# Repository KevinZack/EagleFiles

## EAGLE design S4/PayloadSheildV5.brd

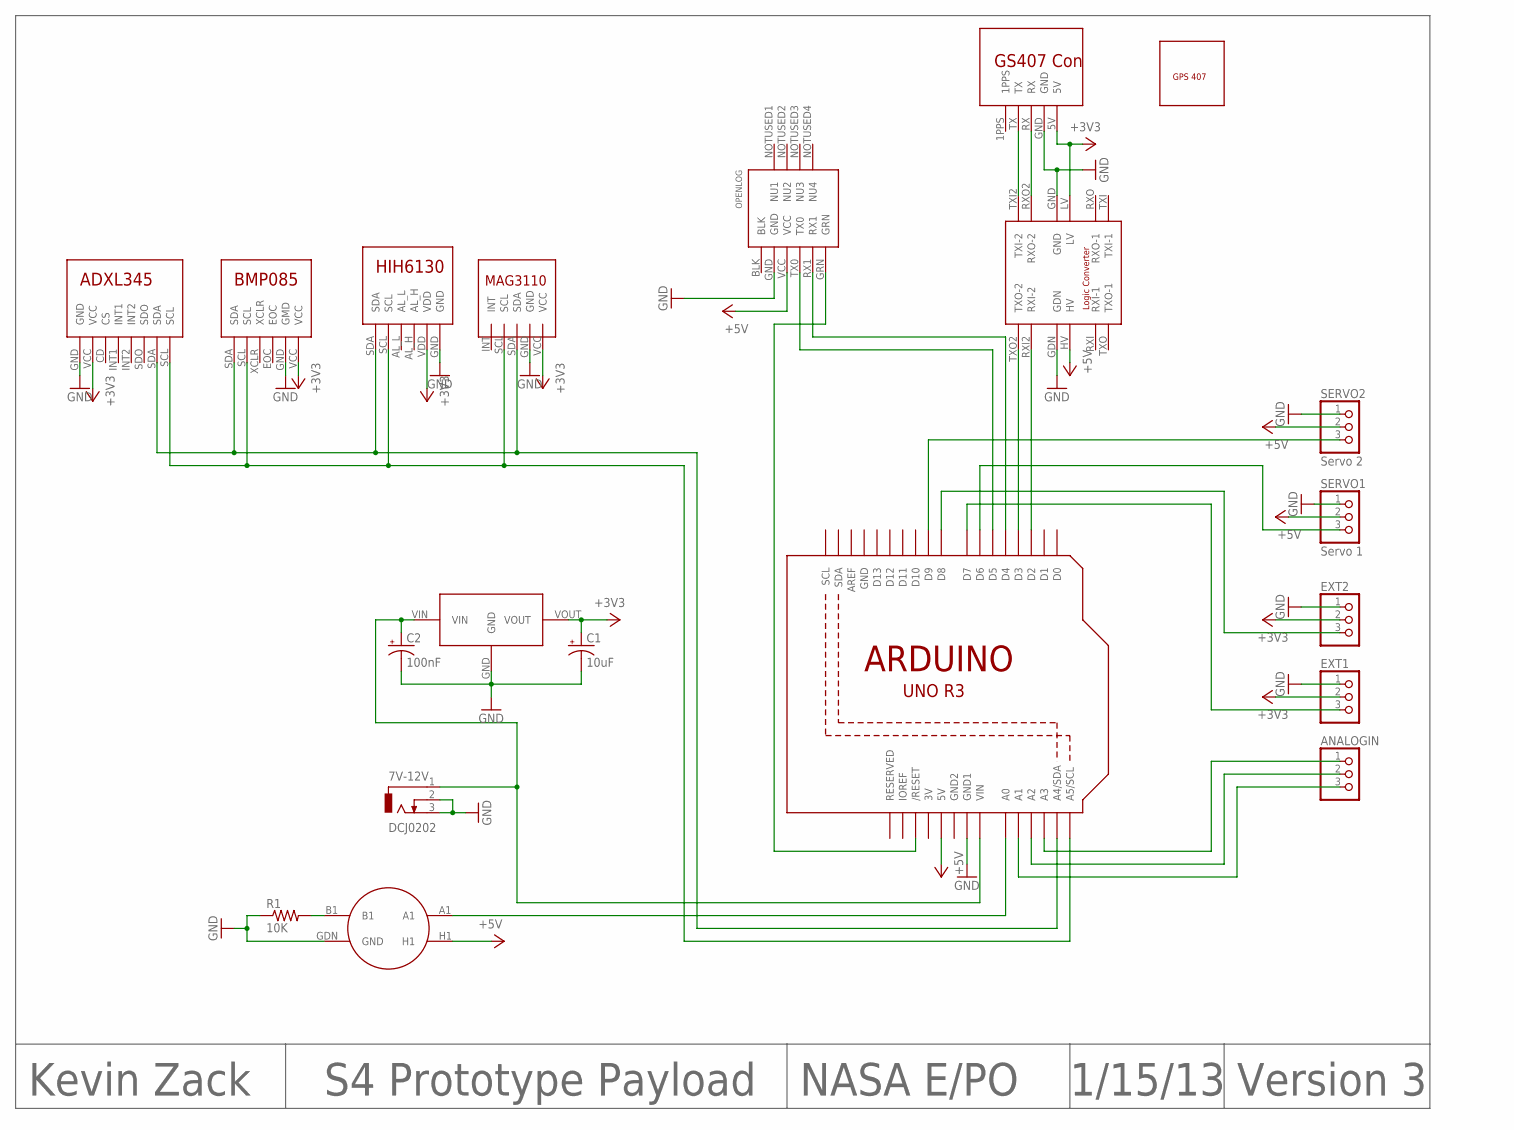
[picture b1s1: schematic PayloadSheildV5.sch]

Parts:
3.3V: LD1117V33
7V-12V: DCJ0202
ADXL345: ADXL345; ADXL345+
ANALOGIN: PINHD-1X3; 1X03
BMP085: BMP085
C1: 10uF; E2,5-6
C2: 100nF; E2,5-6
EXT1, EXT2: PINHD-1X3; 1X03
GASSEN: GAS
GPS: GPS
GPSCON: EM407CONNECTOR
HIH6310: HIH6130
LOGIC: LOGICCONVERTER
MAG3110: MAG3110
OPENLOG: OPENLOG
R1: 10K; 0204/5
SERVO1: Servo 1; 1X03
SERVO2: Servo 2; 1X03
U2: ARDUINOR3

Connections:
3V: U2.3V
+3V3: 3.3V.VOUT, ADXL345.VCC, BMP085.VCC, C1.+, EXT1.2, EXT2.2, GPSCON.5V, HIH6310.VDD, LOGIC.LV, MAG3110.VCC
+5V: GASSEN.H1, LOGIC.HV, OPENLOG.VCC, SERVO1.2, SERVO2.2, U2.5V
GND: 3.3V.GND, 7V-12V.2, 7V-12V.3, ADXL345.GND, BMP085.GND (GMD), C1.-, C2.-, EXT1.1, EXT2.1, GASSEN.GDN (GND), GPSCON.GND, HIH6310.GND, LOGIC.GDN, LOGIC.GND, MAG3110.GND, OPENLOG.GND, R1.1, SERVO1.1, SERVO2.1, U2.GND, U2.GND1
GND2: U2.GND2
unnamed: GASSEN.A1, U2.A0
unnamed: GPSCON.RX, LOGIC.RXO2 (RXO-2)
unnamed: OPENLOG.GRN, U2.RESET (/RESET)
unnamed: GASSEN.B1, R1.2
unnamed: OPENLOG.RX1, U2.D4
unnamed: OPENLOG.TX0, U2.D5
unnamed: SERVO2.3, U2.D9
unnamed: ANALOGIN.1, U2.A3
unnamed: SERVO1.3, U2.D6
unnamed: ANALOGIN.2, U2.A2
unnamed: ANALOGIN.3, U2.A1
unnamed: 3.3V.VIN, 7V-12V.1, C2.+, U2.VIN
unnamed: GPSCON.TX, LOGIC.TXI2 (TXI-2)
unnamed: LOGIC.RXI2 (RXI-2), U2.D2
unnamed: EXT1.3, U2.D7
unnamed: EXT2.3, U2.D8
unnamed: LOGIC.TXO2 (TXO-2), U2.D3
SCL: ADXL345.SCL, BMP085.SCL, HIH6310.SCL, MAG3110.SCL, U2.A5 (A5/SCL)
SDA: ADXL345.SDA, BMP085.SDA, HIH6310.SDA, MAG3110.SDA, U2.A4 (A4/SDA)

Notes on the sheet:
Kevin Zack
NASA E/PO
1/15/13
S4 Prototype Payload
Version 3

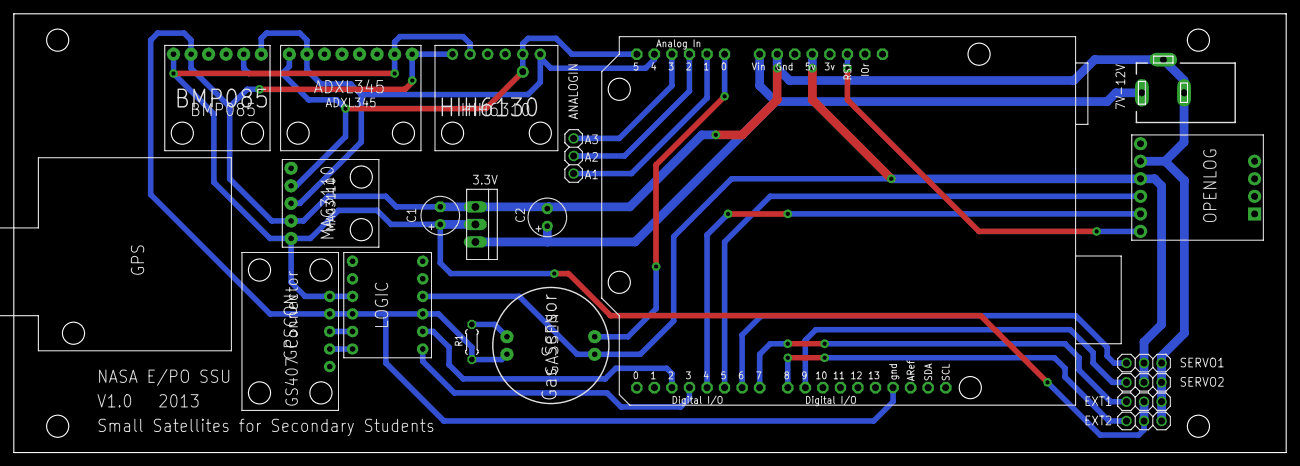
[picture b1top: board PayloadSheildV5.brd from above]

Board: 2 copper layers, 184.2 x 63.5 mm, 20 parts (0 on the bottom side), 22 nets.

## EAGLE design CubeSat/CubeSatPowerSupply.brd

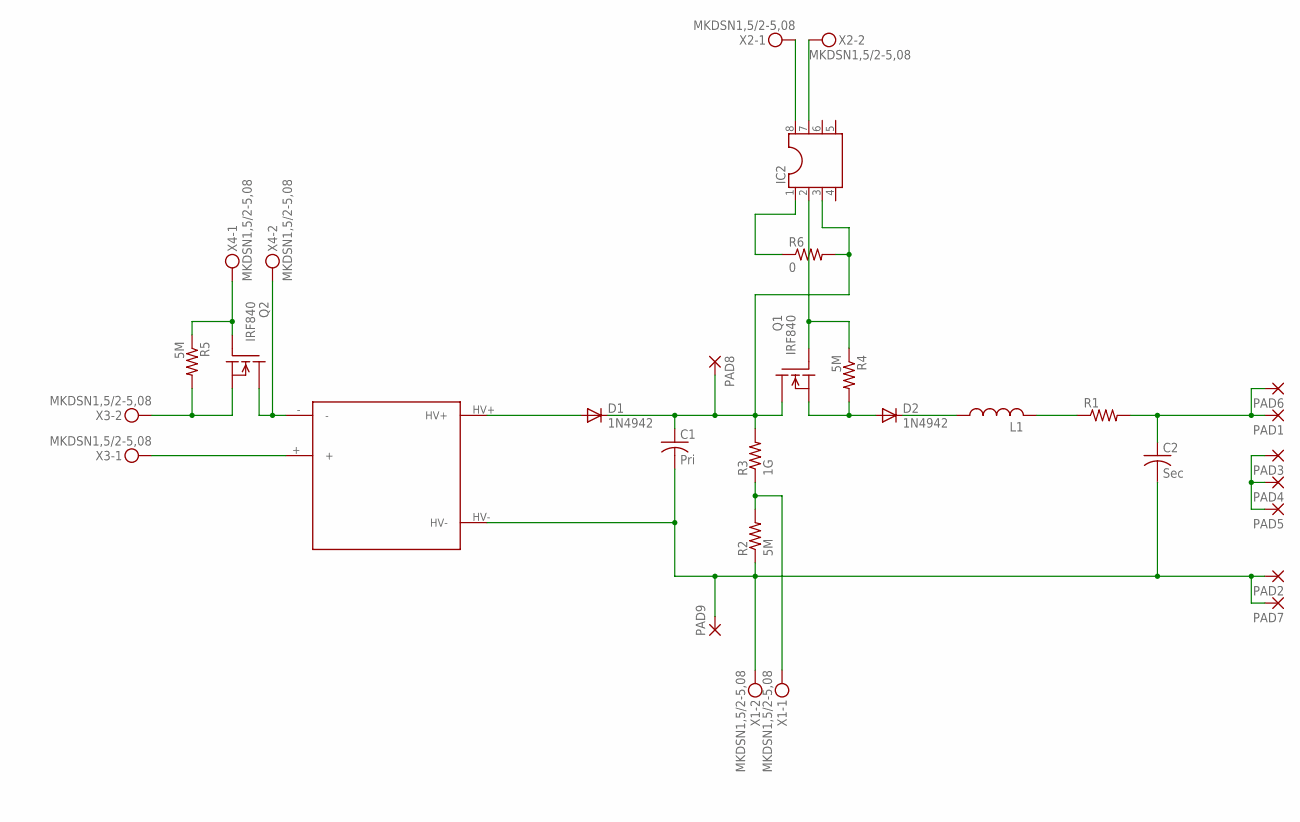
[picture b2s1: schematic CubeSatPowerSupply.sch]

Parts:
C1: Pri; C325-182X374
C2: Sec; C325-182X374
D1, D2: 1N4942; DO41-10
IC2: DIL8; DIL08
L1: L-US0207/12; 0207/12
PAD1, PAD2, PAD3, PAD4, PAD5, PAD6, PAD7, PAD8, PAD9: 2,54/1,0
Q1, Q2: IRF840; TO220
R1: R-US_0309/12; 0309/12
R2, R4, R5: 5M; 0207/10
R3: 1G; 0207/10
R6: 0; 0207/10
U$1: Q5
X1, X2, X3, X4: MKDSN1,5/2-5,08

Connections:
unnamed: L1.2, R1.1
unnamed: D2.C, L1.1
unnamed: C2.1, PAD1.1, PAD6.1, R1.2
unnamed: IC2.2, Q1.1 (G), R4.1
unnamed: D2.A, Q1.3 (S), R4.2
unnamed: C1.1, D1.C, IC2.3, PAD8.1, Q1.2 (D), R3.2, R6.2
unnamed: IC2.1, R6.1
unnamed: Q2.1 (G), R5.1, X4.1
unnamed: D1.A, U$1.HV+
unnamed: R2.2, R3.1, X1.1
unnamed: C1.2, C2.2, PAD2.1, PAD7.1, PAD9.1, R2.1, U$1.HV-, X1.2
unnamed: PAD3.1, PAD4.1, PAD5.1
unnamed: IC2.7, X2.2
unnamed: IC2.8, X2.1
unnamed: Q2.3 (S), R5.2, X3.2
unnamed: Q2.2 (D), U$1.-, X4.2
unnamed: U$1.+, X3.1

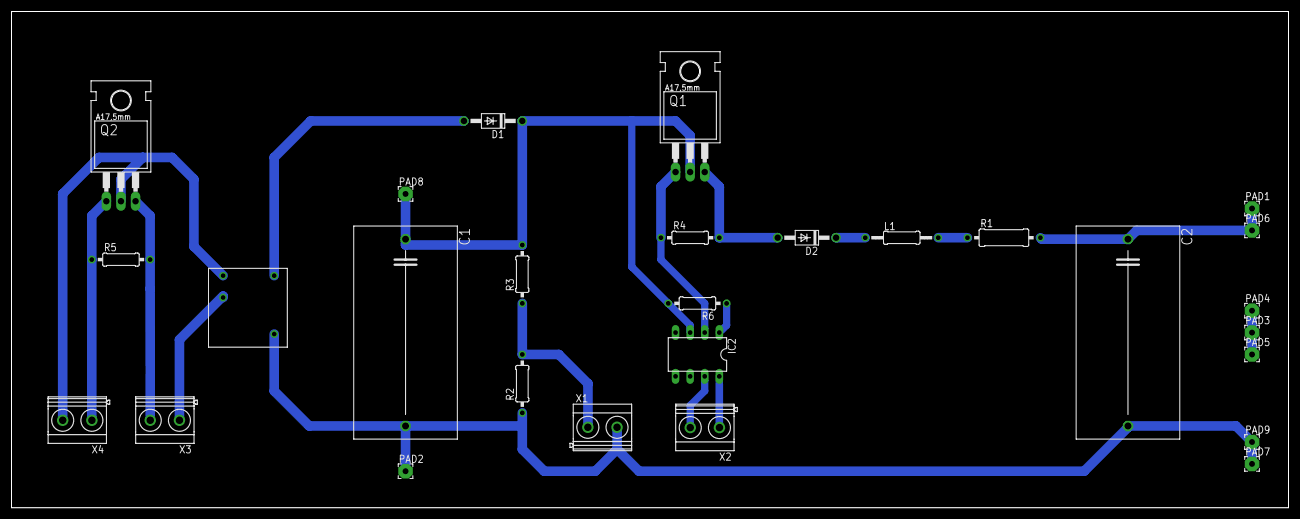
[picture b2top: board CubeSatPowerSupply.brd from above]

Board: 2 copper layers, 222.2 x 86.4 mm, 28 parts (0 on the bottom side), 17 nets.

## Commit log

2013-01-27 First Commit
    Only S4 Files
2013-02-01 Updated S4 Files + garber
2013-02-03 Added Cubesat files
2013-02-06 ready to print
